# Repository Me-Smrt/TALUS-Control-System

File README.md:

# TALUS — Distributed Humanoid Robotics Platform

Welcome to my contribution to **TALUS**, a project of Tennessee Tech's [Autonomous Robotics Club (ARC)](https://www.instagram.com/tntecharc/)! This repository showcases my independently developed hardware, software, and simulation work for the project.

In the interest of transparency, much of the documentation was written with the help of AI (credit where it's due! 🤣), but the engineering work represented here is my own.
I hope you find the project interesting as you explore the repository! I also plan to add photos of TALUS and demonstrations of the simulations as the project progresses.

---

TALUS is an experimental humanoid/automaton platform for on-campus information assistance, conversational interaction, deterministic visual perception, and safely mediated robot behaviors. The intended primary use is answering questions about **Tennessee Tech** and interacting with people on campus.

> **R&D / safety status:** This repository includes hardware designs, draft control firmware, AI software, computer vision, and Blender simulations. Passing source-level tests does **not** establish that actuator power, emergency-stop paths, collision prevention, or complete motion are validated on physical hardware. Physical motion must remain disabled until formal bench verification.

## Authorship and project background

TALUS is part of the work of Tennessee Tech's Autonomous Robotics Club (ARC). **This repository showcases my individual engineering contribution to TALUS**, including the electronics and PCB designs, distributed control architecture, original firmware, AI/voice integration, computer vision and kinematics software, simulation tools, and operator dashboard. I developed and integrated these TALUS-specific components independently.

The project also builds on excellent work from the wider robotics and open-source communities. InMoov, the Will Cogley head, external CAD and URDF references, machine-learning models, and software dependencies remain the work of their respective creators. See [Third-party acknowledgments](THIRD_PARTY_NOTICES.md) for details.

**Development began before this Git repository.** The first commit is a snapshot of work already developed and tested locally, rather than the project's starting date. [Authorship and development history](AUTHORSHIP.md) provides context for earlier milestones.

**Author:** Tyler Krumm · [GitHub profile](https://github.com/Me-Smrt)

## How the system is divided

| Directory | Responsibility |
| --- | --- |
| [`Design/`](Design/) | KiCad CCB and RCB design files, project-local symbols/footprints and text-based manufacturing documentation (3D vendor assets are not committed) |
| [`Model/`](Model/) | InMoov and optional Will Cogley head Blender builder scripts; generated models are local-only |
| [`Software/Raspberry PI 5/`](Software/Raspberry%20PI%205/) | Pi 5 hardware authority: Supervisor UART, GPIO heartbeat, SocketCAN and RCB sessions |
| [`Software/Central Control Module/`](Software/Central%20Control%20Module/) | CCB safety-supervisor firmware draft |
| [`Software/Remote Control Module/`](Software/Remote%20Control%20Module/) | RCB firmware draft: CAN, local PWM/servo safety, UID/role pairing |
| [`Software/CV R&D/`](Software/CV%20R%26D/) | Pi-side MediaPipe perception, IK/retargeting, state API, Blender simulation |
| [`Software/Auxiliary Processor R&D/`](Software/Auxiliary%20Processor%20R%26D/) | Local Qwen, STT/TTS, engagement, YOLO tracking, world state, campus knowledge |
| [`Software/Dashboard/`](Software/Dashboard/) | Flask operator interface and authenticated read-only status/diagnostics |

## Authority boundaries

```text
Pi cameras / MediaPipe / deterministic IK
              |                          AUX computer: Qwen / Whisper / Kokoro / YOLO
              |                                |
              +-- Pi control & state API <----+ (semantic behavior requests only)
                             |
                    CCB safety supervisor
                             |
                   CAN channels -> RCBs -> actuators

Flask dashboard -> authenticated status / camera / diagnostics APIs
```

The AUX AI **cannot** directly write raw servo positions, CAN/PWM commands, arm state, power enables, or emergency-stop controls. The Pi behavior layer is responsible for deterministic arbitration and safety checks; independent CCB/RCB safeguards remain mandatory.

## Current development capabilities

- Local LLM reasoning, offline speech recognition and voice-selectable TTS; spoken readiness cue before accepting conversation input.
- Experimental full-duplex acoustic echo cancellation and barge-in; **live hardware validation remains outstanding**.
- Pi-owned camera stream, MediaPipe pose/facial expression data, and Blender retargeting.
- Low-rate YOLO-based anonymous person/object tracking with timestamped world-state snapshots; background perception is deterministic rather than Qwen-driven.
- Local Tennessee Tech knowledge retrieval through SQLite FTS5; source documents can be rebuilt into a runtime database.
- Experimental Blender gestures, simplified arm-collision screening, and IK stability limits; **not physical safety certification**.
- CCB/RCB and Pi control firmware drafts with deliberate hardware-actuation development locks.

See [Project Status](PROJECT_STATUS.md) for what remains to be tested.

## Getting started

1. Choose a subsystem from the table above and follow its component README for installation and configuration. Components may require separate Python environments or PlatformIO toolchains.
2. Obtain the AI model weights, vendor CAD references, and Blender head assets listed in the relevant component README. These are **not** included in this source-only repository.
3. For AUX console testing, see [`Software/Auxiliary Processor R&D/README.md`](Software/Auxiliary%20Processor%20R%26D/README.md); for Pi CV and Blender simulation, see [`Software/CV R&D/README.md`](Software/CV%20R%26D/README.md).

4. For the CCB and RCB KiCad projects, see the [hardware design README](Design/README.md) for project files, footprint libraries, and optional 3D models.

### 3D Component Models

This repository includes the editable KiCad hardware designs, symbols, and footprints, but excludes externally sourced STEP models to keep the repository lightweight. These models are used for 3D visualization and mechanical reference and can be downloaded from their respective manufacturers. Their absence does not affect the electrical schematic or PCB layout.

### Licensing at a glance

I'm sharing my original TALUS software and Blender builder/helper scripts under the **Mozilla Public License 2.0 (MPL-2.0)**. You're welcome to explore, use, and build on that work under the terms of the license. Its file-level sharing requirements help improvements to the covered code remain available to others.

My original Central Control Module and Remote Control Module KiCad designs are shared under the **CERN Open Hardware Licence v2 — Weakly Reciprocal (CERN-OHL-W-2.0)**. Third-party footprints, symbols, component models, and other upstream material keep their own terms. See [Licensing by component](LICENSE_SCOPE.md), [Hardware design licensing](Design/LICENSING.md), and [Third-party acknowledgments](THIRD_PARTY_NOTICES.md).

## Source-only distribution and authorship

Blender project files (`.blend`), AI model weights, CAD input meshes, vendor STEP files, local runtime databases and generated packages are intentionally excluded. Builder scripts and component READMEs describe how to obtain or generate locally required assets; the Will Cogley head builder may require manually supplied reference files not available from automated downloads.

See [Third-party acknowledgments](THIRD_PARTY_NOTICES.md) for the external projects and libraries that informed or support TALUS. Each component retains the credit and license appropriate to its source.

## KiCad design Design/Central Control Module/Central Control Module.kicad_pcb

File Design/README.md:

# TALUS — KiCad Hardware Designs

This directory contains the editable hardware source for the **Central Control Module (CCB)** and **Remote Control Module (RCB)** used in TALUS's distributed robot-control architecture. The designs are research and development work; publishing the source does not establish that the boards or their actuator safety systems have been validated on physical hardware.

## Projects

| Project | Open in KiCad | Purpose |
| --- | --- | --- |
| **Central Control Module (CCB)** | [`Central Control Module.kicad_pro`](Central%20Control%20Module/Central%20Control%20Module.kicad_pro) | Raspberry Pi interface, supervisor, distributed CAN channels, remote power, and safety control. |
| **Remote Control Module (RCB)** | [`Remote Control Module.kicad_pro`](Remote%20Control%20Module/Remote%20Control%20Module.kicad_pro) | Remote CAN communications, local servo/PWM control, power management, and hardware safety interfaces. |

Each project directory includes the main schematic, hierarchical schematic sheets, PCB layout, KiCad project configuration, and project-local library content where applicable. `Footprints/` contains supplementary imported component symbols and footprints, including material supplied by third parties.

## Opening and inspecting the designs

1. Install a compatible version of **KiCad** (the projects have been developed with KiCad 10).
2. Open the relevant `.kicad_pro` file through KiCad's Project Manager.
3. Inspect the schematic and PCB layout in their respective editors. Recheck electrical and design rules in your own environment before using the files for fabrication.
4. If a custom footprint or symbol is unresolved, check the project's local `.pretty` library, `fp-lib-table`, and library paths. Libraries imported from `Footprints/` may need to be registered or their paths adjusted for your computer.

Some library and 3D-model references may reflect the author's local development paths. Prefer project-relative paths (such as `${KIPRJMOD}`) where practical, and do not assume an externally downloaded file will be present after cloning.

## Footprints and 3D models

The repository intentionally includes the **editable KiCad symbols and footprints**, but excludes externally sourced `.step` / `.stp` component models and manufacturing exports. You can edit the electrical design and generate fabrication files without the vendor STEP geometry. The 3D Viewer may display missing models until you obtain those assets separately and update their paths.

When retrieving external symbols, footprints, or 3D files, use the original vendor or library provider and respect their license and attribution requirements. The existence of a file in `Footprints/` does not mean it was created or relicensed by the TALUS author.

## Safety and licensing

The CCB and RCB include circuitry intended to manage actuator power, communication timeouts, and servo authorization. These features require hardware bring-up and verification; they should **not** be treated as a guarantee of physical safety based on the published design files alone.

Original hardware design contributions are distributed under **CERN-OHL-W-2.0**. Third-party content retains its own terms. See [hardware licensing and scope](LICENSING.md), the [license text](LICENSE), [repository-wide licensing](../LICENSE_SCOPE.md), and [third-party acknowledgments](../THIRD_PARTY_NOTICES.md).

For the broader development and verification boundaries, see [Project Status](../PROJECT_STATUS.md).

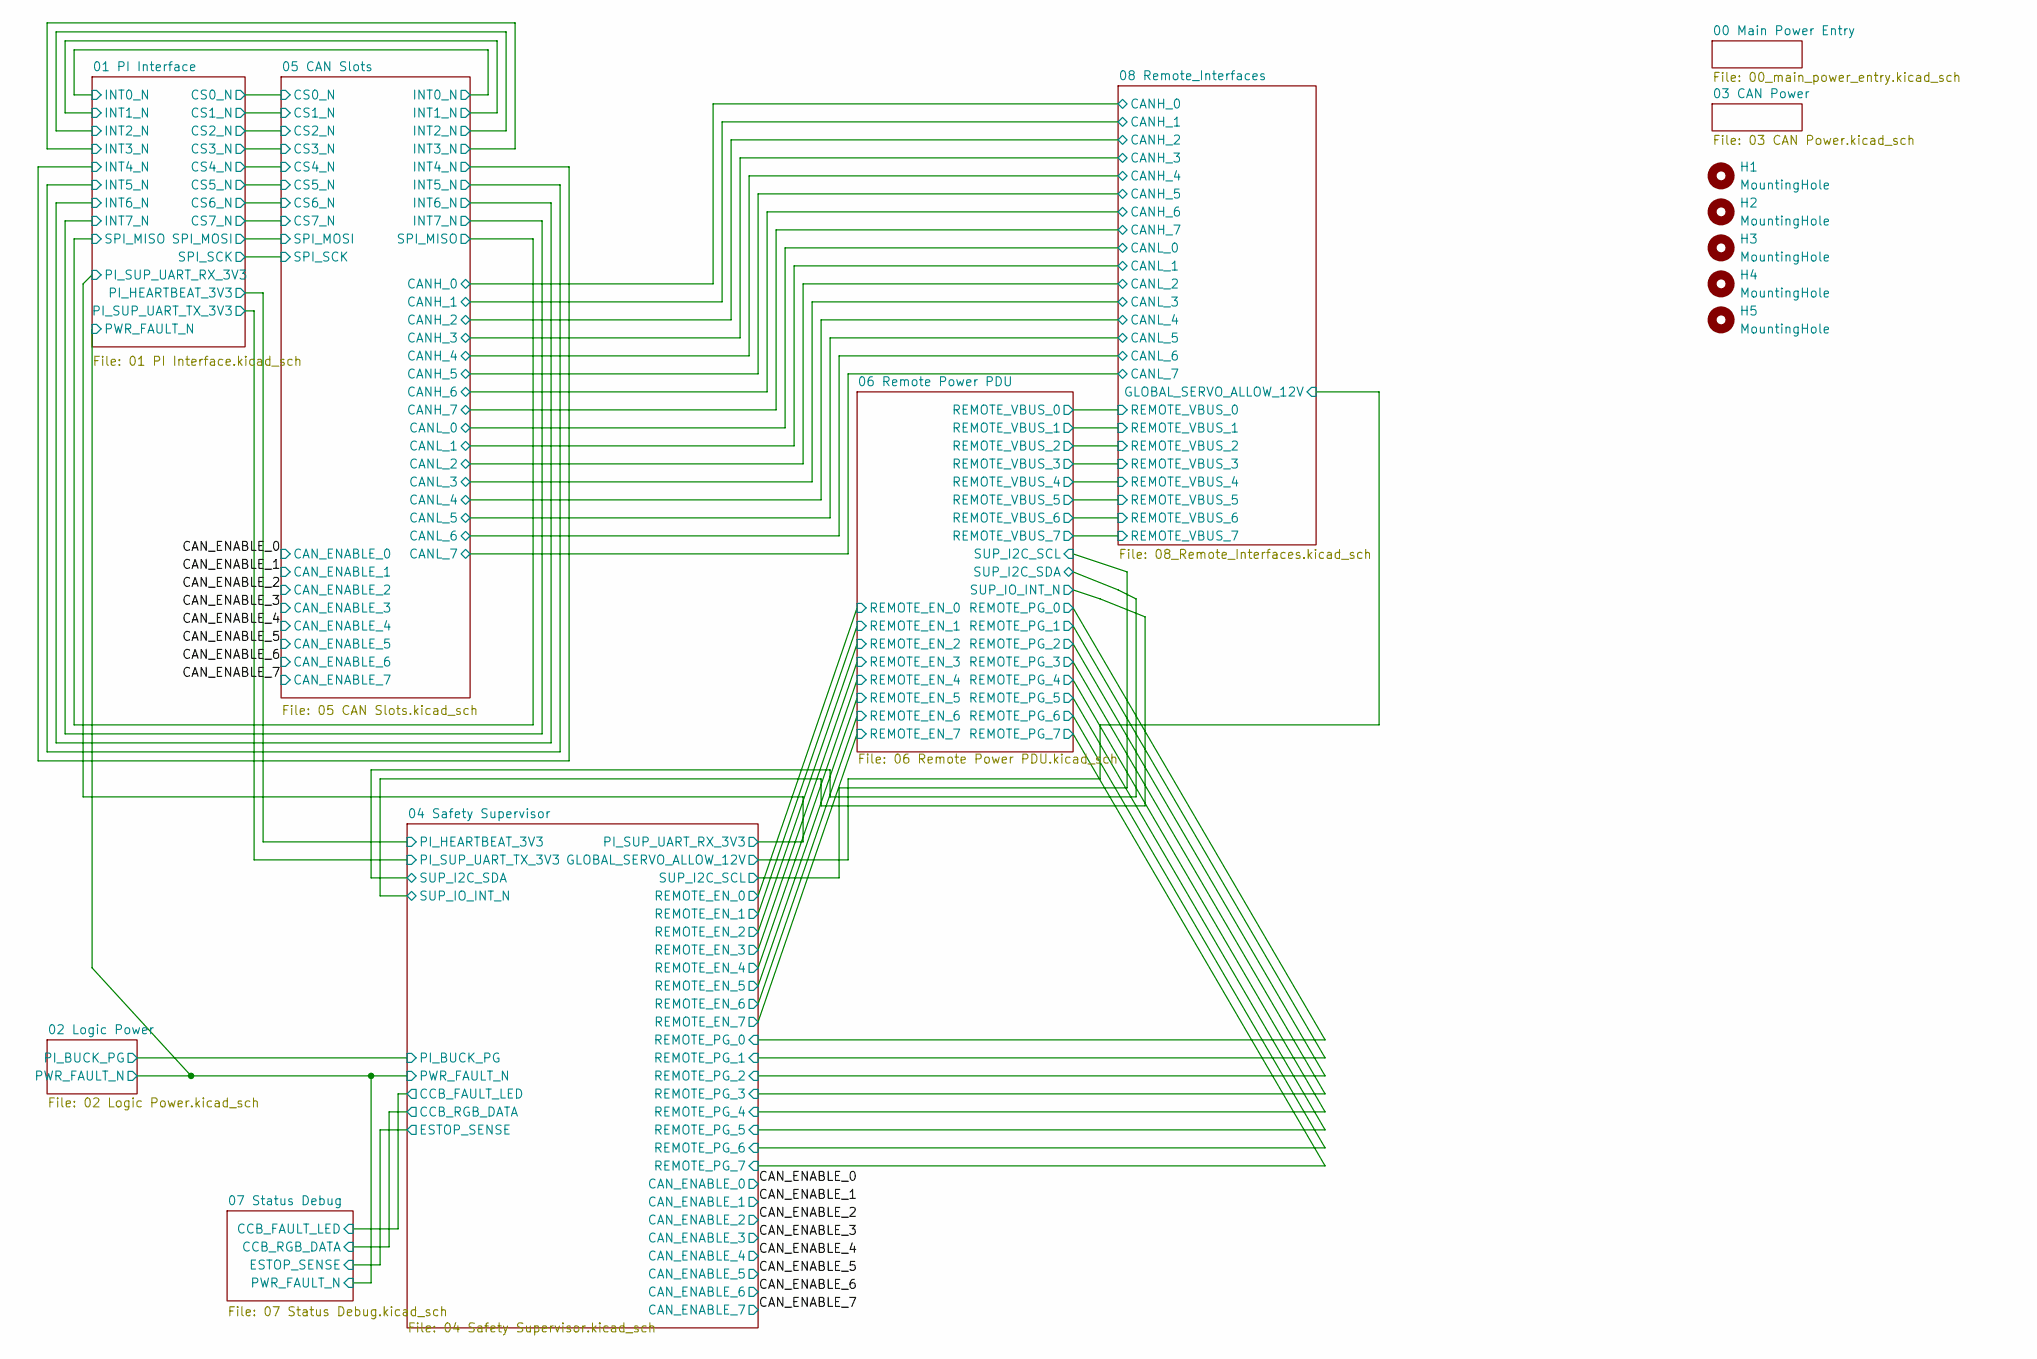
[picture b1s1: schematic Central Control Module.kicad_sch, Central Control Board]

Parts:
H1, H2, H3, H4, H5: MountingHole; MountingHole_3.2mm_M3

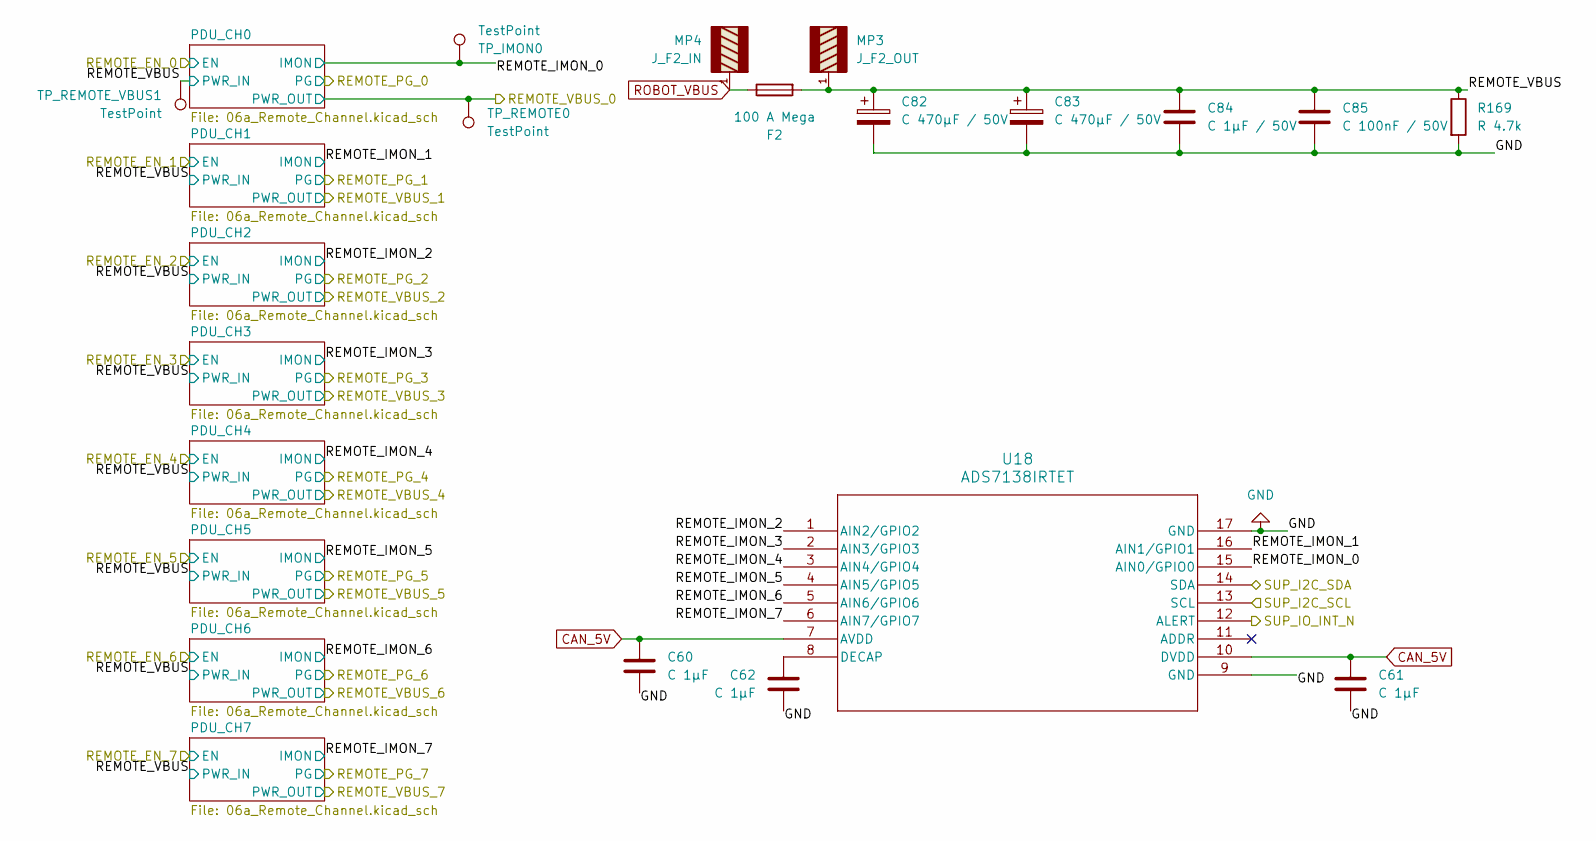
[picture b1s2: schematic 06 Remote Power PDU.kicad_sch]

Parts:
C60, C61, C62: C 1µF; C_0805_2012Metric; MPN C2012X7R1H105K085AC
C82, C83: C 470µF / 50V; CAP_PAN_12.5X20_PAN; MPN EEU-FR1H471B
C84: C 1µF / 50V; C_1206_3216Metric; MPN GRM31CR71H105KA61L
C85: C 100nF / 50V; C_0603_1608Metric; MPN GRM188R72A104KA35D
F2: 100 A Mega
MP3: J_F2_OUT; WP-BUTR_7461084; MPN 7461084
MP4: J_F2_IN; WP-BUTR_7461084; MPN 7461084
R169: R 4.7k; R_1206_3216Metric; MPN RC1206FR-074K7L
TP_IMON0: TestPoint; TestPoint_Pad_D1.5mm
TP_REMOTE0: TestPoint; TestPoint_Pad_D1.5mm
TP_REMOTE_VBUS1: TestPoint; TestPoint_Pad_D1.5mm
U18: ADS7138IRTET; MPN ADS7138IRTET

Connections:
/04 Safety Supervisor/SUP_I2C_SCL: U18.13 (SCL); also elsewhere on the board
/04 Safety Supervisor/SUP_I2C_SDA: U18.14 (SDA); also elsewhere on the board
/04 Safety Supervisor/SUP_IO_INT_N: U18.12 (ALERT); also elsewhere on the board
/06 Remote Power PDU/REMOTE_IMON_0: TP_IMON0.1 (1_1), U18.15 (AIN0/GPIO0); also elsewhere on the board
/06 Remote Power PDU/REMOTE_IMON_1: U18.16 (AIN1/GPIO1); also elsewhere on the board
/06 Remote Power PDU/REMOTE_IMON_2: U18.1 (AIN2/GPIO2); also elsewhere on the board
/06 Remote Power PDU/REMOTE_IMON_3: U18.2 (AIN3/GPIO3); also elsewhere on the board
/06 Remote Power PDU/REMOTE_IMON_4: U18.3 (AIN4/GPIO4); also elsewhere on the board
/06 Remote Power PDU/REMOTE_IMON_5: U18.4 (AIN5/GPIO5); also elsewhere on the board
/06 Remote Power PDU/REMOTE_IMON_6: U18.5 (AIN6/GPIO6); also elsewhere on the board
/06 Remote Power PDU/REMOTE_IMON_7: U18.6 (AIN7/GPIO7); also elsewhere on the board
/06 Remote Power PDU/REMOTE_VBUS: C82.1, C83.1, C84.1, C85.1, F2.2, MP3.1, R169.1, TP_REMOTE_VBUS1.1 (1_1); also elsewhere on the board
/06 Remote Power PDU/REMOTE_VBUS_0: TP_REMOTE0.1 (1_1); also elsewhere on the board
CAN_5V: C60.1, C61.1, U18.7 (AVDD), U18.10 (DVDD); also elsewhere on the board
GND: C60.2, C61.2, C62.2, C82.2, C83.2, C84.2, C85.2, R169.2, U18.9 (GND), U18.17 (GND); also elsewhere on the board
unnamed: C62.1, U18.8 (DECAP)
ROBOT_VBUS: F2.1, MP4.1; also elsewhere on the board

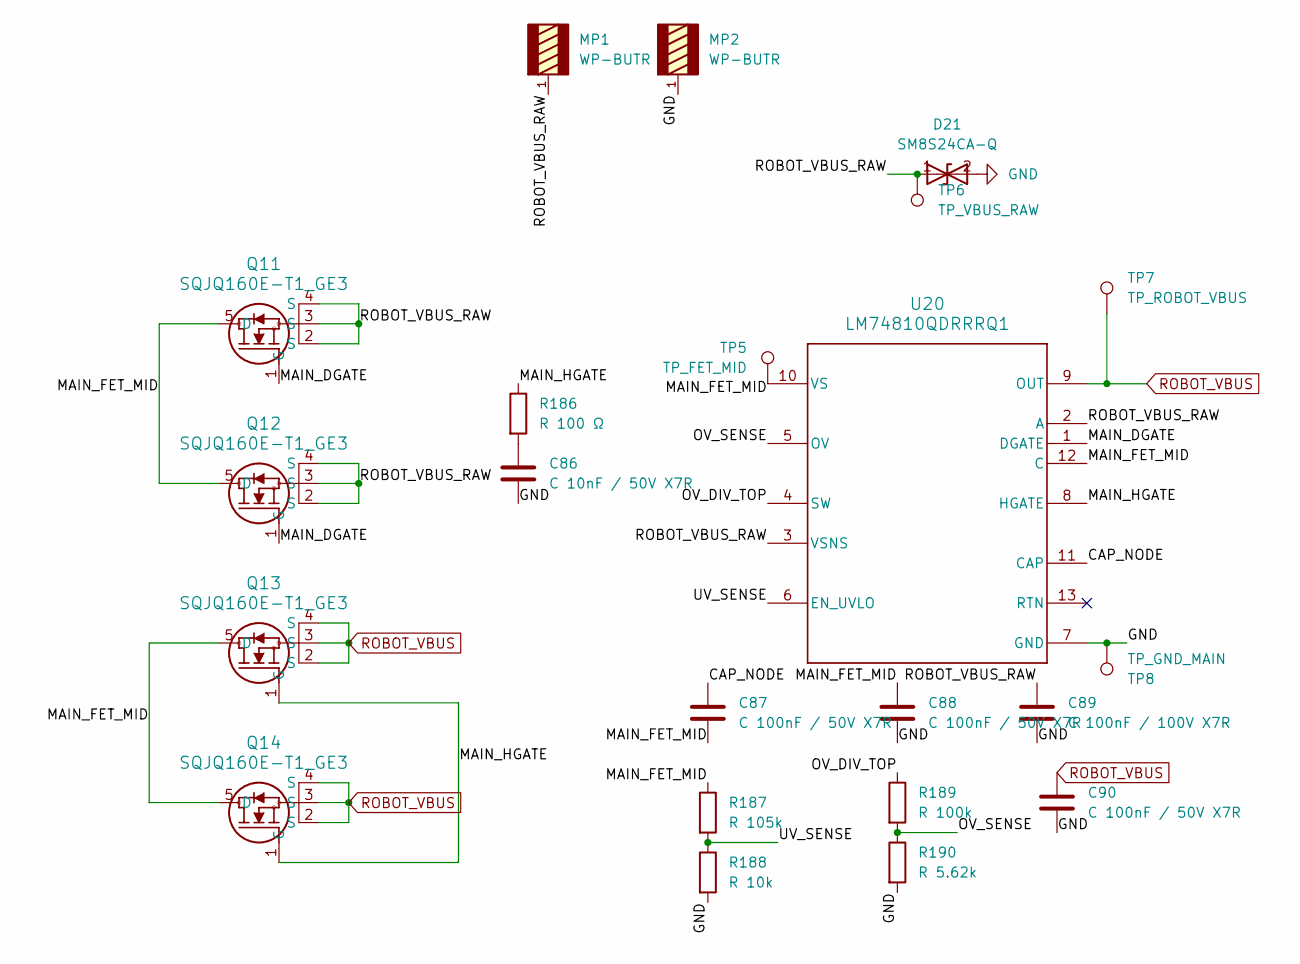
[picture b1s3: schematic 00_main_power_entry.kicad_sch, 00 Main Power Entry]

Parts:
C86: C 10nF / 50V X7R; C_0603_1608Metric; MPN GRM188R71H103KA01D
C87, C88, C90: C 100nF / 50V X7R; C_0603_1608Metric; MPN GRM188R72A104KA35D
C89: C 100nF / 100V X7R; C_0805_2012Metric; MPN GCD21BR72A104KA01L
D21: SM8S24CA-Q; Bourns_SM8S-Q_DO-218; MPN SM8S24CA-Q
MP1, MP2: WP-BUTR; WP-BUTR_7461084; MPN 7461084
Q11, Q12, Q13, Q14: SQJQ160E-T1_GE3; DPAK_0E-T1_GE3_VIS; MPN SQJQ160E-T1_GE3
R186: R 100 Ω; R_0603_1608Metric; MPN RC0603FR-07100RL
R187: R 105k; R_0603_1608Metric; MPN RC0603FR-07105KL
R188: R 10k; R_0603_1608Metric; MPN RC0603FR-0710KL
R189: R 100k; R_0603_1608Metric; MPN RC0603FR-07100KL
R190: R 5.62k; R_0603_1608Metric; MPN RC0603FR-075K62L
TP5: TP_FET_MID; TestPoint_Pad_D1.5mm
TP6: TP_VBUS_RAW; TestPoint_Pad_D1.5mm
TP7: TP_ROBOT_VBUS; TestPoint_Pad_D1.5mm
TP8: TP_GND_MAIN; TestPoint_Pad_D1.5mm
U20: LM74810QDRRRQ1; DRR0012E-MFG; MPN LM74810QDRRRQ1

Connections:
/00 Main Power Entry/CAP_NODE: C87.1, U20.11 (CAP)
/00 Main Power Entry/MAIN_DGATE: Q11.1 (G), Q12.1 (G), U20.1 (DGATE)
/00 Main Power Entry/MAIN_FET_MID: C87.2, C88.1, Q11.5 (D), Q12.5 (D), Q13.5 (D), Q14.5 (D), R187.1, TP5.1 (1_1), U20.10 (VS), U20.12 (C)
/00 Main Power Entry/MAIN_HGATE: Q13.1 (G), Q14.1 (G), R186.1, U20.8 (HGATE)
/00 Main Power Entry/OV_DIV_TOP: R189.1, U20.4 (SW)
/00 Main Power Entry/OV_SENSE: R189.2, R190.1, U20.5 (OV)
/00 Main Power Entry/ROBOT_VBUS_RAW: C89.1, D21.1 (A1), MP1.1, Q11.2 (S), Q11.3 (S), Q11.4 (S), Q12.2 (S), Q12.3 (S), Q12.4 (S), TP6.1 (1_1), U20.2 (A), U20.3 (VSNS)
/00 Main Power Entry/UV_SENSE: R187.2, R188.1, U20.6 (EN_UVLO)
GND: C86.2, C88.2, C89.2, C90.2, D21.2 (A2), MP2.1, R188.2, R190.2, TP8.1 (1_1), U20.7 (GND); also elsewhere on the board
unnamed: C86.1, R186.2
ROBOT_VBUS: C90.1, Q13.2 (S), Q13.3 (S), Q13.4 (S), Q14.2 (S), Q14.3 (S), Q14.4 (S), TP7.1 (1_1), U20.9 (OUT); also elsewhere on the board

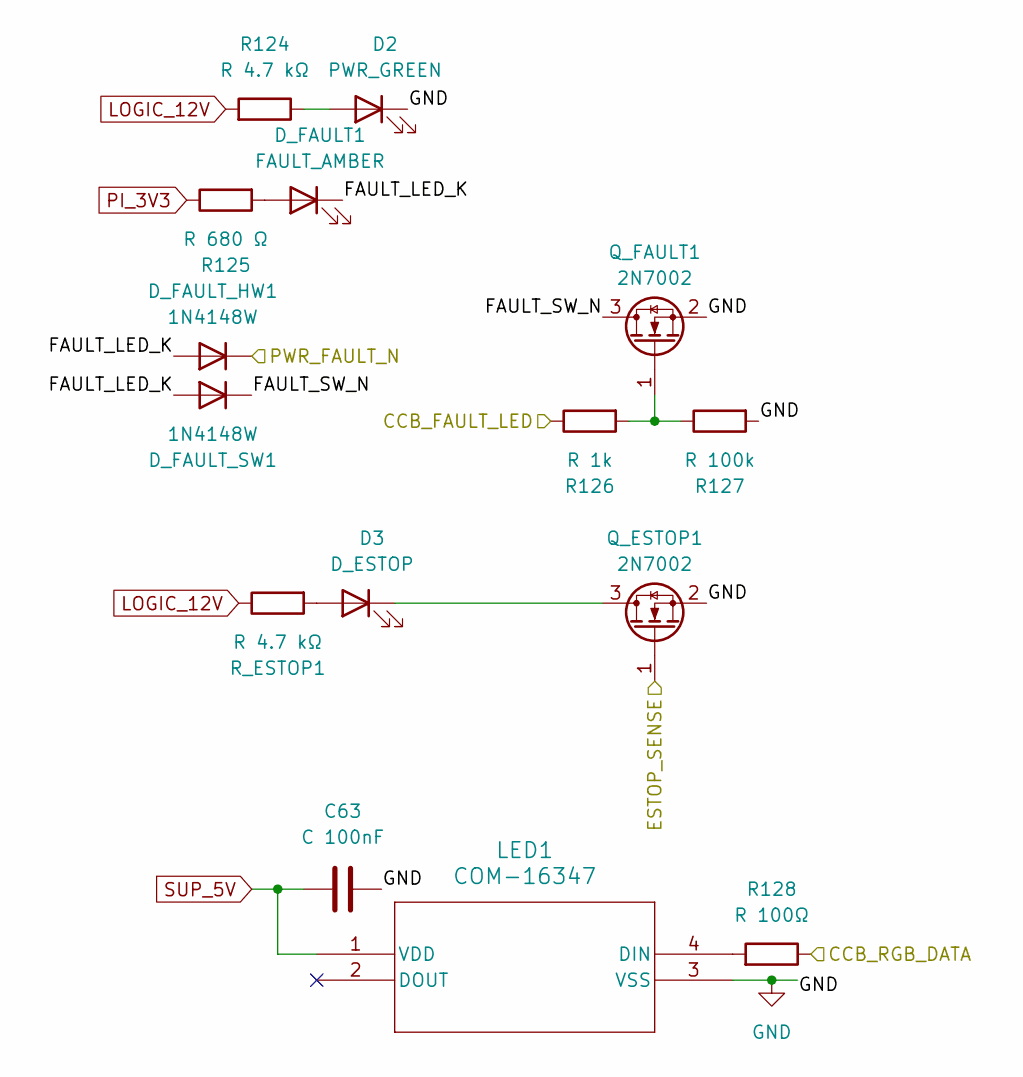
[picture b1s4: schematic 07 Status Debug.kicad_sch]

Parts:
C63: C 100nF; C_0603_1608Metric; MPN GRM188R72A104KA35D
D2: PWR_GREEN; LED_0603_1608Metric; MPN LTST-C190KGKT
D3: D_ESTOP; LED_0603_1608Metric; MPN LTST-C190KRKT
D_FAULT1: FAULT_AMBER; LED_0603_1608Metric; MPN LTST-C190KSKT
D_FAULT_HW1: 1N4148W; D_SOD-123; MPN 1N4148W-7-F
D_FAULT_SW1: 1N4148W; D_SOD-123; MPN 1N4148W-7-F
LED1: COM-16347; COM-16347_SPK; MPN COM-16347
Q_ESTOP1: 2N7002; SOT-23; MPN 2N7002LT1G
Q_FAULT1: 2N7002; SOT-23; MPN 2N7002LT1G
R124: R 4.7 kΩ; R_0603_1608Metric; MPN RC0603FR-074K7L
R125: R 680 Ω; R_0603_1608Metric; MPN RC0603FR-07680RL
R126: R 1k; R_0603_1608Metric; MPN RC0603FR-071KL
R127: R 100k; R_0603_1608Metric; MPN RC0603FR-07100KL
R128: R 100Ω; R_0603_1608Metric; MPN RC0603FR-07100RL
R_ESTOP1: R 4.7 kΩ; R_0603_1608Metric; MPN RC0603FR-074K7L

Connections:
/01 PI Interface/PWR_FAULT_N: D_FAULT_HW1.1 (K); also elsewhere on the board
/04 Safety Supervisor/CCB_FAULT_LED: R126.1; also elsewhere on the board
/04 Safety Supervisor/CCB_RGB_DATA: R128.1; also elsewhere on the board
/04 Safety Supervisor/ESTOP_SENSE: Q_ESTOP1.1 (G); also elsewhere on the board
/07 Status Debug/FAULT_LED_K: D_FAULT1.1 (K), D_FAULT_HW1.2 (A), D_FAULT_SW1.2 (A)
/07 Status Debug/FAULT_SW_N: D_FAULT_SW1.1 (K), Q_FAULT1.3 (D)
GND: C63.2, D2.1 (K), LED1.3 (VSS), Q_ESTOP1.2 (S), Q_FAULT1.2 (S), R127.2; also elsewhere on the board
LOGIC_12V: R124.2, R_ESTOP1.1; also elsewhere on the board
unnamed: D2.2 (A), R124.1
unnamed: D3.2 (A), R_ESTOP1.2
unnamed: D3.1 (K), Q_ESTOP1.3 (D)
unnamed: D_FAULT1.2 (A), R125.2
unnamed: LED1.4 (DIN), R128.2
unnamed: Q_FAULT1.1 (G), R126.2, R127.1
PI_3V3: R125.1; also elsewhere on the board
SUP_5V: C63.1, LED1.1 (VDD); also elsewhere on the board

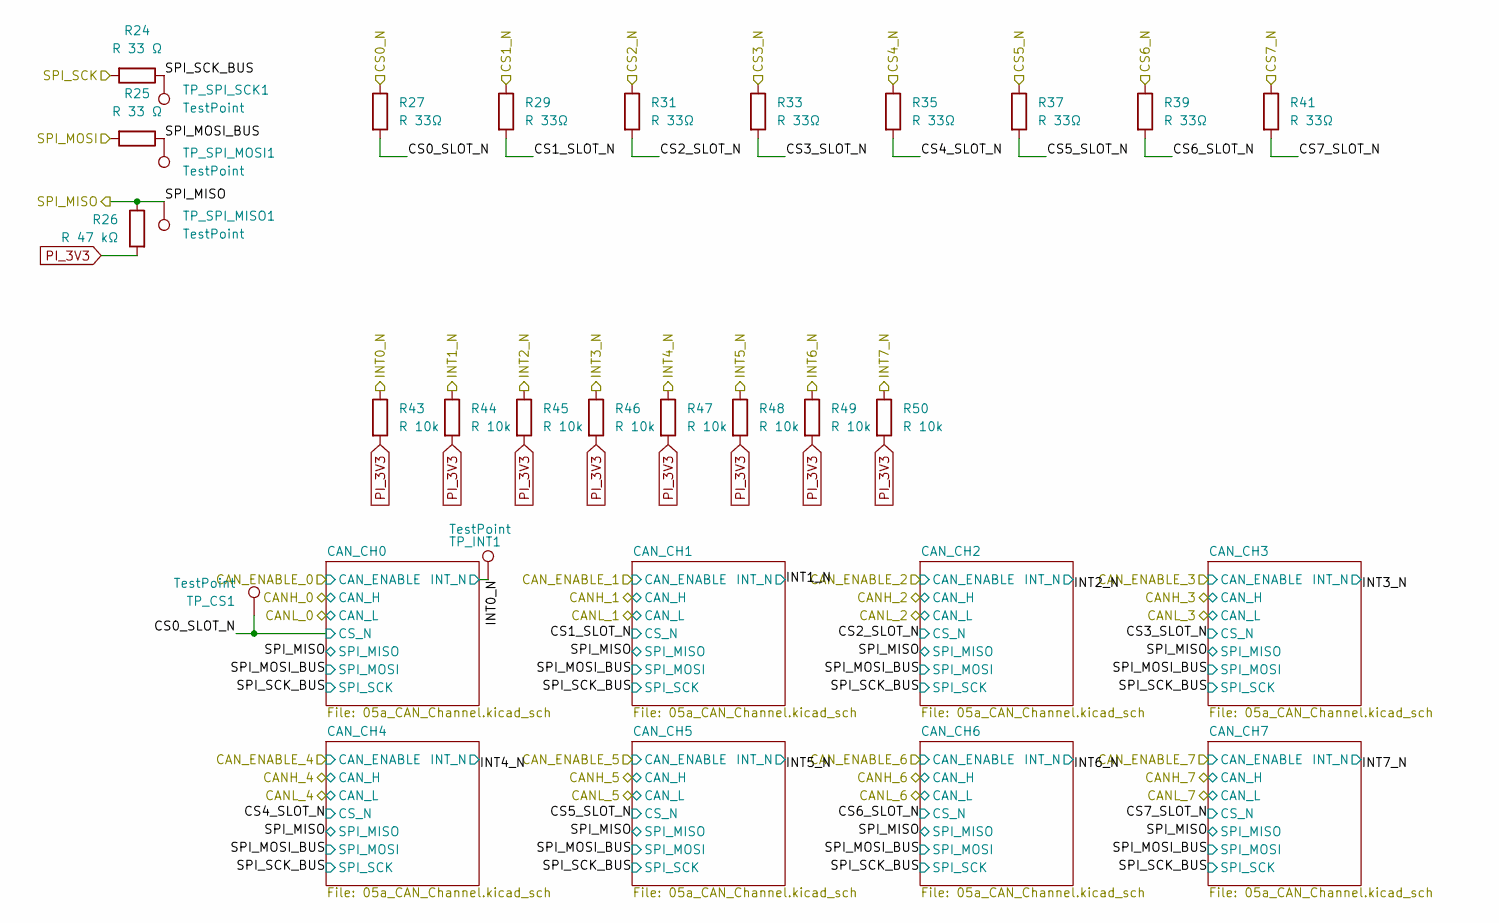
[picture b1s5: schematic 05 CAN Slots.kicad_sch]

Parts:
R24, R25: R 33 Ω; R_0603_1608Metric; MPN RC0603FR-0733RL
R26: R 47 kΩ; R_0603_1608Metric; MPN RC0603FR-0747KL
R27, R29, R31, R33, R35, R37, R39, R41: R 33Ω; R_0603_1608Metric; MPN RC0603FR-0733RL
R43, R44, R45, R46, R47, R48, R49, R50: R 10k; R_0603_1608Metric; MPN RC0603FR-0710KL
TP_CS1: TestPoint; TestPoint_Pad_D1.5mm
TP_INT1: TestPoint; TestPoint_Pad_D1.5mm
TP_SPI_MISO1: TestPoint; TestPoint_Pad_D1.5mm
TP_SPI_MOSI1: TestPoint; TestPoint_Pad_D1.5mm
TP_SPI_SCK1: TestPoint; TestPoint_Pad_D1.5mm

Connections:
/01 PI Interface/CS0_N: R27.1; also elsewhere on the board
/01 PI Interface/CS1_N: R29.1; also elsewhere on the board
/01 PI Interface/CS2_N: R31.1; also elsewhere on the board
/01 PI Interface/CS3_N: R33.1; also elsewhere on the board
/01 PI Interface/CS4_N: R35.1; also elsewhere on the board
/01 PI Interface/CS5_N: R37.1; also elsewhere on the board
/01 PI Interface/CS6_N: R39.1; also elsewhere on the board
/01 PI Interface/CS7_N: R41.1; also elsewhere on the board
/01 PI Interface/INT0_N: R43.1, TP_INT1.1 (1_1); also elsewhere on the board
/01 PI Interface/INT1_N: R44.1; also elsewhere on the board
/01 PI Interface/INT2_N: R45.1; also elsewhere on the board
/01 PI Interface/INT3_N: R46.1; also elsewhere on the board
/01 PI Interface/INT4_N: R47.1; also elsewhere on the board
/01 PI Interface/INT5_N: R48.1; also elsewhere on the board
/01 PI Interface/INT6_N: R49.1; also elsewhere on the board
/01 PI Interface/INT7_N: R50.1; also elsewhere on the board
/01 PI Interface/SPI_MISO: R26.1, TP_SPI_MISO1.1 (1_1); also elsewhere on the board
/01 PI Interface/SPI_MOSI: R25.2; also elsewhere on the board
/01 PI Interface/SPI_SCK: R24.2; also elsewhere on the board
/05 CAN Slots/CS0_SLOT_N: R27.2, TP_CS1.1 (1_1); also elsewhere on the board
/05 CAN Slots/CS1_SLOT_N: R29.2; also elsewhere on the board
/05 CAN Slots/CS2_SLOT_N: R31.2; also elsewhere on the board
/05 CAN Slots/CS3_SLOT_N: R33.2; also elsewhere on the board
/05 CAN Slots/CS4_SLOT_N: R35.2; also elsewhere on the board
/05 CAN Slots/CS5_SLOT_N: R37.2; also elsewhere on the board
/05 CAN Slots/CS6_SLOT_N: R39.2; also elsewhere on the board
/05 CAN Slots/CS7_SLOT_N: R41.2; also elsewhere on the board
/05 CAN Slots/SPI_MOSI_BUS: R25.1, TP_SPI_MOSI1.1 (1_1); also elsewhere on the board
/05 CAN Slots/SPI_SCK_BUS: R24.1, TP_SPI_SCK1.1 (1_1); also elsewhere on the board
PI_3V3: R26.2, R43.2, R44.2, R45.2, R46.2, R47.2, R48.2, R49.2, R50.2; also elsewhere on the board

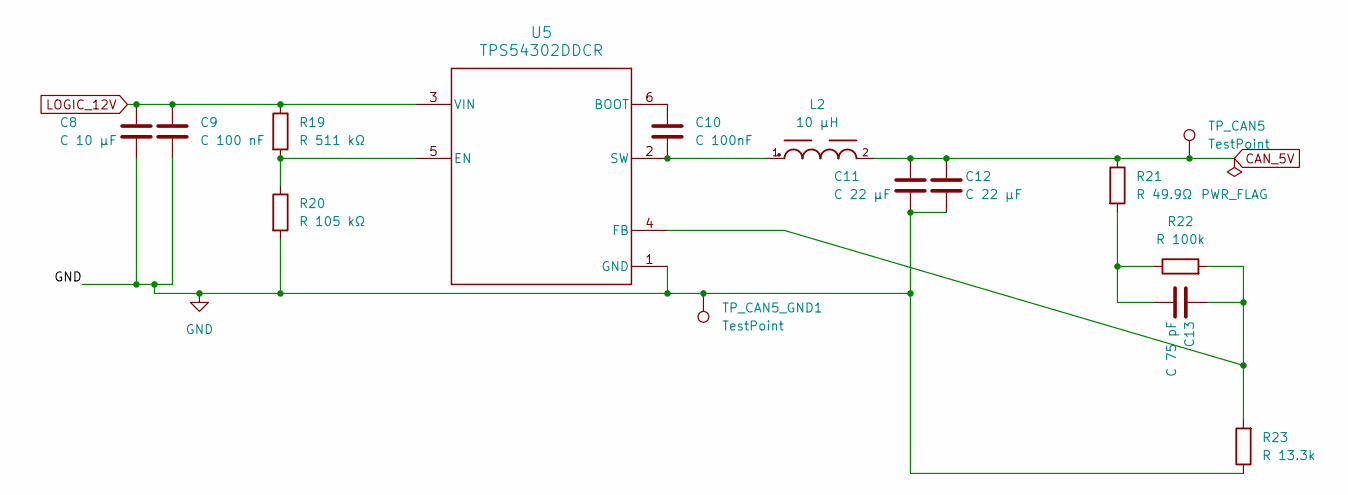
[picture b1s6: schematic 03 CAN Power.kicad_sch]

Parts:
C8: C 10 µF; C_1206_3216Metric; MPN C3216X7R1H106K160AC
C9: C 100 nF; C_0603_1608Metric; MPN GRM188R72A104KA35D
C10: C 100nF; C_0603_1608Metric; MPN GRM188R72A104KA35D
C11, C12: C 22 µF; C_1206_3216Metric; MPN TMK316BBJ226ML-T
C13: C 75 pF; C_0603_1608Metric; MPN GCM1885C2A750JA16D
L2: 10 µH; 7447714100; MPN 7447714100
R19: R 511 kΩ; R_0603_1608Metric; MPN RC0603FR-07511KL
R20: R 105 kΩ; R_0603_1608Metric; MPN RC0603FR-07105KL
R21: R 49.9Ω; R_0603_1608Metric; MPN RC0603FR-0749R9L
R22: R 100k; R_0603_1608Metric; MPN RC0603FR-07100KL
R23: R 13.3k; R_0603_1608Metric; MPN RC0603FR-0713K3L
TP_CAN5, TP_CAN5_GND1: TestPoint; TestPoint_Pad_D1.5mm
U5: TPS54302DDCR; MPN TPS54302DDCR

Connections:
CAN_5V: C11.1, C12.1, L2.2, R21.1, TP_CAN5.1 (1_1); also elsewhere on the board
GND: C8.2, C9.2, C11.2, C12.2, R20.2, R23.1, TP_CAN5_GND1.1 (1_1), U5.1 (GND); also elsewhere on the board
LOGIC_12V: C8.1, C9.1, R19.1, U5.3 (VIN); also elsewhere on the board
unnamed: C13.2, R21.2, R22.1
unnamed: C10.1, U5.6 (BOOT)
unnamed: R19.2, R20.1, U5.5 (EN)
unnamed: C13.1, R22.2, R23.2, U5.4 (FB)
unnamed: C10.2, L2.1, U5.2 (SW)

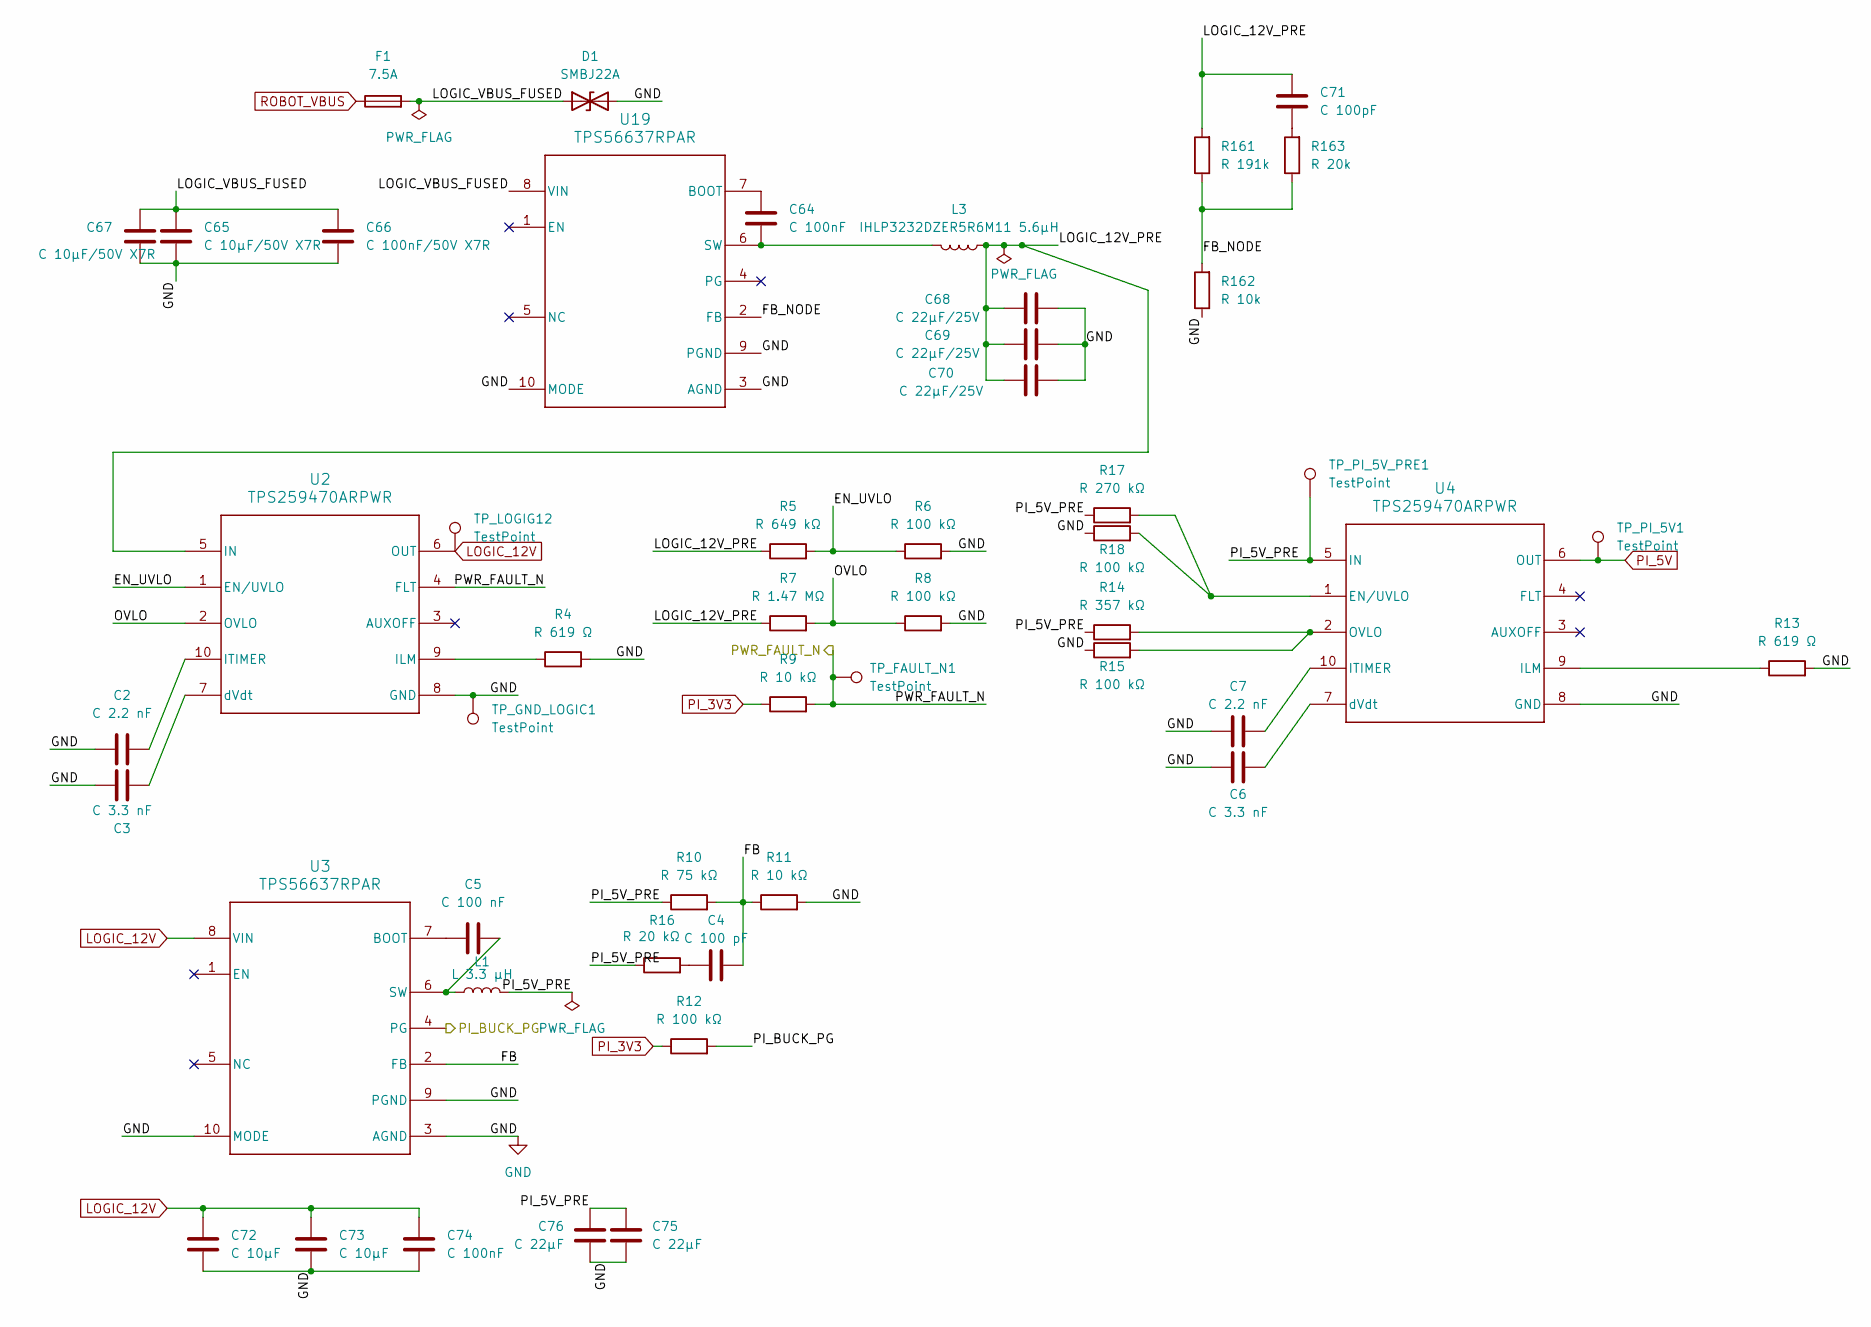
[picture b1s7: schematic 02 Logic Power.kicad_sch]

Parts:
C2, C7: C 2.2 nF; C_0603_1608Metric; MPN GRM188R72A222KA01D
C3, C6: C 3.3 nF; C_0603_1608Metric; MPN GRM188R72A332KA01D
C4: C 100 pF; C_0603_1608Metric; MPN GCM1885C1H101FA16D
C5: C 100 nF; C_0603_1608Metric; MPN GRM188R72A104KA35D
C64, C74: C 100nF; C_0603_1608Metric; MPN GRM188R72A104KA35D
C65, C67: C 10µF/50V X7R; C_1206_3216Metric; MPN C3216X7R1H106K160AC
C66: C 100nF/50V X7R; C_0603_1608Metric; MPN GRM188R72A104KA35D
C68, C69, C70: C 22µF/25V; C_1206_3216Metric; MPN TMK316BBJ226ML-T
C71: C 100pF; C_0603_1608Metric; MPN GCM1885C1H101FA16D
C72, C73: C 10µF; C_1206_3216Metric; MPN C3216X7R1H106K160AC
C75, C76: C 22µF; C_1206_3216Metric; MPN TMK316BBJ226ML-T
D1: SMBJ22A; D_SMB; MPN SMBJ22A
F1: 7.5A; CONN2_164.0001_LTF; MPN 178.6164.0001
L1: L 3.3 µH; L_Vishay_IHLP-3232; MPN IHLP3232DZER3R3M11
L3: IHLP3232DZER5R6M11 5.6µH; L_Vishay_IHLP-3232; MPN IHLP3232DZER5R6M11
R4, R13: R 619 Ω; R_0603_1608Metric; MPN RC0603FR-07619RL
R5: R 649 kΩ; R_0603_1608Metric; MPN RC0603FR-07649KL
R6, R8, R12, R15, R18: R 100 kΩ; R_0603_1608Metric; MPN RC0603FR-07100KL
R7: R 1.47 MΩ; R_0603_1608Metric; MPN RC0603FR-071M47L
R9, R11: R 10 kΩ; R_0603_1608Metric; MPN RC0603FR-0710KL
R10: R 75 kΩ; R_0603_1608Metric; MPN RC0603FR-0775KL
R14: R 357 kΩ; R_0603_1608Metric; MPN RC0603FR-07357KL
R16: R 20 kΩ; R_0603_1608Metric; MPN RC0603FR-0720KL
R17: R 270 kΩ; R_0603_1608Metric; MPN RC0603FR-07270KL
R161: R 191k; R_0603_1608Metric; MPN RC0603FR-07191KL
R162: R 10k; R_0603_1608Metric; MPN RC0603FR-0710KL
R163: R 20k; R_0603_1608Metric; MPN RC0603FR-0720KL
TP_FAULT_N1: TestPoint; TestPoint_Pad_D1.5mm
TP_GND_LOGIC1: TestPoint; TestPoint_Pad_D1.5mm
TP_LOGIG12: TestPoint; TestPoint_Pad_D1.5mm
TP_PI_5V1, TP_PI_5V_PRE1: TestPoint; TestPoint_Pad_D1.5mm
U2, U4: TPS259470ARPWR; MPN TPS259470ARPWR
U3, U19: TPS56637RPAR; MPN TPS56637RPAR

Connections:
/01 PI Interface/PWR_FAULT_N: R9.2, TP_FAULT_N1.1 (1_1), U2.4 (FLT); also elsewhere on the board
/02 Logic Power/EN_UVLO: R5.2, R6.1, U2.1 (EN/UVLO)
/02 Logic Power/FB: C4.2, R10.2, R11.1, U3.2 (FB)
/02 Logic Power/FB_NODE: R161.1, R162.2, R163.1, U19.2 (FB)
/02 Logic Power/LOGIC_12V_PRE: C68.1, C69.1, C70.1, C71.2, L3.1, R5.1, R7.1, R161.2, U2.5 (IN)
/02 Logic Power/LOGIC_VBUS_FUSED: C65.1, C66.1, C67.1, D1.1 (A1), F1.2, U19.8 (VIN)
/02 Logic Power/OVLO: R7.2, R8.1, U2.2 (OVLO)
/02 Logic Power/PI_5V_PRE: C75.1, C76.1, L1.2, R10.1, R14.1, R16.1, R17.1, TP_PI_5V_PRE1.1 (1_1), U4.5 (IN)
/02 Logic Power/PI_BUCK_PG: R12.2, U3.4 (PG); also elsewhere on the board
GND: C2.1, C3.1, C6.1, C7.1, C65.2, C66.2, C67.2, C68.2, C69.2, C70.2, C72.2, C73.2, C74.2, C75.2, C76.2, D1.2 (A2), R4.2, R6.2, R8.2, R11.2, R13.2, R15.1, R18.1, R162.1, TP_GND_LOGIC1.1 (1_1), U2.8 (GND), U3.3 (AGND), U3.9 (PGND), U3.10 (MODE), U4.8 (GND), U19.3 (AGND), U19.9 (PGND), U19.10 (MODE); also elsewhere on the board
LOGIC_12V: C72.1, C73.1, C74.1, TP_LOGIG12.1 (1_1), U2.6 (OUT), U3.8 (VIN); also elsewhere on the board
unnamed: C4.1, R16.2
unnamed: C71.1, R163.2
unnamed: R4.1, U2.9 (ILM)
unnamed: C2.2, U2.10 (ITIMER)
unnamed: C3.2, U2.7 (dVdt)
unnamed: C5.1, U3.7 (BOOT)
unnamed: C5.2, L1.1, U3.6 (SW)
unnamed: R17.2, R18.2, U4.1 (EN/UVLO)
unnamed: R13.1, U4.9 (ILM)
unnamed: C7.2, U4.10 (ITIMER)
unnamed: R14.2, R15.2, U4.2 (OVLO)
unnamed: C6.2, U4.7 (dVdt)
unnamed: C64.1, U19.7 (BOOT)
unnamed: C64.2, L3.2, U19.6 (SW)
PI_3V3: R9.1, R12.1; also elsewhere on the board
PI_5V: TP_PI_5V1.1 (1_1), U4.6 (OUT); also elsewhere on the board
ROBOT_VBUS: F1.1; also elsewhere on the board
